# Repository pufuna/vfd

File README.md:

# PUFVFD — преобразователь частоты 1,5 кВт

Вход: 1 фаза 220 В. Выход: 3 фазы 0…220 В, 0…200 Гц. Скалярное (U/f) и бездатчиковое векторное управление, ПИД-регулятор, ЖКИ 20×4 на русском языке, Modbus RTU, Wi-Fi (веб-интерфейс, Modbus TCP), Bluetooth, корпус для 3D-печати.

> **Статус проекта.** Это комплект конструкторской документации и программного обеспечения. Алгоритмы управления проверены на математической модели двигателя, обе прошивки собираются, печатная плата разведена и проходит проверку правил KiCad без замечаний. **Устройство не собиралось, плата не изготавливалась, на реальном железе ничего не испытывалось.** Плата разведена автоматически и не проходила ревью человеком. Подробности — в `docs/01_description.md` (разделы 3.6 и 4.2).
>
> В устройстве действуют опасные напряжения. Сборка и наладка требуют квалификации для работы с сетевым напряжением.

## Состав

| Путь | Содержимое |
|---|---|
| `pdf/` | все документы в PDF одной папкой: схемы, чертежи слоёв платы, карта сверловки, описание, сборка и наладка, руководство, Modbus, параметры, перечень, даташит модуля (пересборка — `python3 tools/make_pdf.py`) |
| `hardware/out/pch1500_eskd.pdf` | комплект схем по ЕСКД: Э1 (структурная), Э3 (принципиальная, 5 листов), ПЭ3 (перечень элементов), Э4 (соединений) |
| `hardware/out/*.svg` | те же листы по отдельности |
| `hardware/pcb/pch1500_a1.kicad_pcb` | печатная плата (проект KiCad 7) |
| `hardware/pcb/out/` | Gerber и сверловка (`pch1500_a1_gerber.zip`), координаты элементов, чертежи слоёв, отчёт DRC |
| `hardware/out/pch1500.net` | нетлист KiCad |
| `docs/01_description.md` | техническое описание, расчёты, принцип работы |
| `docs/02_assembly.md` | заказ платы, сборка, прошивка, пошаговая наладка |
| `docs/03_user_manual.md` | руководство по эксплуатации: характеристики, подключение, пульт, подробное описание каждого параметра, аварии, Modbus, Wi-Fi/Bluetooth, примеры применения, лист записи настроек (создаётся `python3 tools/make_manual.py` из `tools/manual/` и таблицы параметров прошивки; PDF — `pdf/08_user_manual.pdf`) |
| `docs/04_modbus.md` | карта регистров Modbus, HTTP API |
| `docs/05_printing.md` | печать корпуса на 3D-принтере: какой комплект STL выбрать, материал, настройки, крепёж, сборка |
| `docs/parameters.md` | таблица параметров и кодов аварий (создаётся из прошивки) |
| `docs/bom.md` | перечень элементов с ориентировочными ценами |
| `docs/netlist.md` | таблица цепей платы |
| `firmware/stm32` | прошивка контроллера (STM32F411 Black Pill) |
| `firmware/esp32` | прошивка модуля связи (ESP32) |
| `firmware/bin` | готовые файлы прошивки STM32 и ESP32 и как их записать без PlatformIO |
| `firmware/sim` | модель двигателя и тесты (`make test`) |
| `enclosure/` | корпус 210 × 230 мм: `pch1500_case.scad`; готовые к печати `stl/whole/` (цельный, стол от 235 × 215 мм), `stl/split/` (разрезной, стол 220 × 220 мм), `stl/common/`; `build_stl.sh` — выпуск STL; `check_fit.py` — проверка, что детали платы не задевают корпус, дисплей и кнопки |

## Основные решения

- Силовая часть: мост KBPC3510, шина 3 × 470 мкФ 400 В, интеллектуальный модуль IGBT IKCM30F60GA (600 В, 30 А) с встроенной защитой от КЗ, автономный тормозной ключ.
- Управление: STM32F411 на гальванически развязанной стороне; развязка ШИМ оптронами HCPL-2630, токи — датчиками Холла ACS712, напряжение шины — изолирующим усилителем.
- Связь: ESP32 как необязательный модуль; привод работает и без него.
- Единый источник данных: схема описана в `hardware/netlist.py`; из него получаются чертежи (с автоматической сверкой связности), перечни и плата.
- Ориентировочная стоимость комплектующих — около 14 850 ₽ (см. `docs/bom.md`; цены и наличие по каталогам не сверялись).

## Пересборка

Чертежи и перечни:

```bash
python3 hardware/gen.py
```

```bash
python3 hardware/sch/docs.py
```

Плата (размещение, трассировка, полигоны и DRC, выходные файлы; нужен KiCad 7 с модулем `pcbnew`):

```bash
python3 hardware/pcb/make_pcb.py place
```

```bash
python3 hardware/pcb/make_pcb.py route
```

```bash
python3 hardware/pcb/make_pcb.py finish
```

```bash
hardware/pcb/export.sh
```

Тесты прошивки и таблица параметров:

```bash
make -C firmware/sim test docs
```

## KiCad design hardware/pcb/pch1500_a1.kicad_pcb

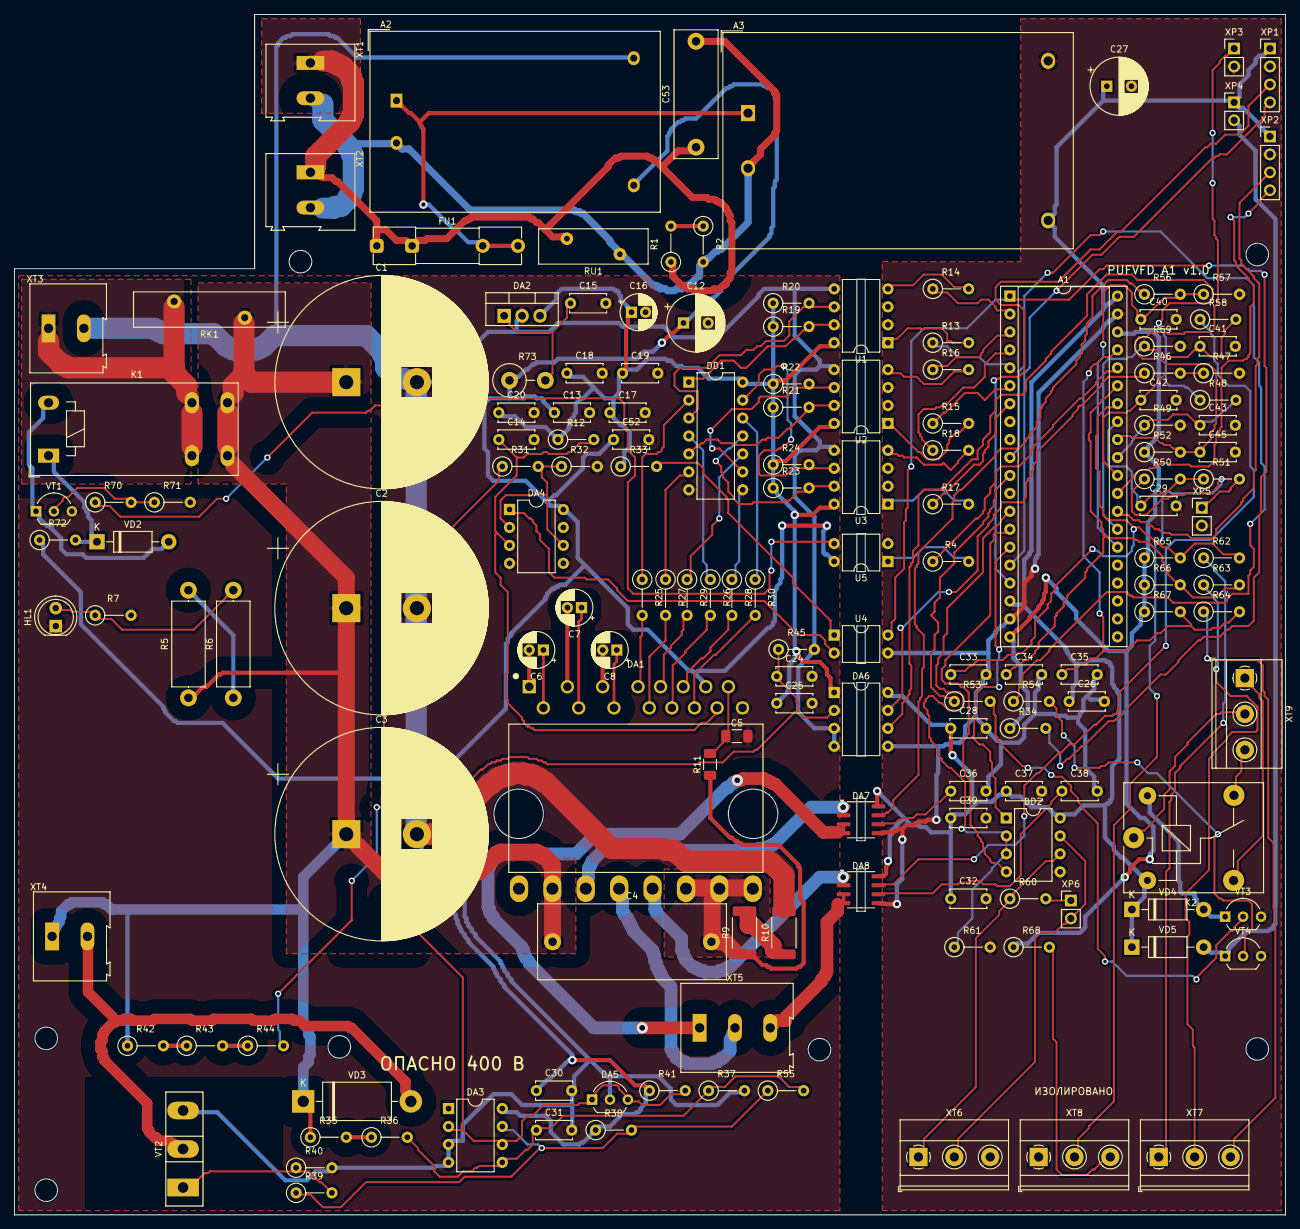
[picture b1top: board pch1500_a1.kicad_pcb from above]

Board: 2 copper layers, 180.0 x 170.0 mm, 164 parts (0 on the bottom side), 119 nets.

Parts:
A1: Black Pill F411; DIP-40_W15.24mm_Socket
A2: HLK-5M15; Converter_ACDC_Hi-Link_HLK-5Mxx
A3: HLK-10M05; Converter_ACDC_Hi-Link_HLK-10Mxx
C1, C2, C3: 470 мкФ 400 В; CP_Radial_D30.0mm_P10.00mm_SnapIn
C4: 0,47 мкФ 630 В; C_Rect_L26.5mm_W10.5mm_P22.50mm_MKS4
C5: 1,5 нФ 1206; C_1206_3216Metric_Pad1.33x1.80mm_HandSolder
C6, C7, C8: 22 мкФ 35 В; CP_Radial_D5.0mm_P2.00mm
C12: 100 мкФ 35 В; CP_Radial_D8.0mm_P3.50mm
C13, C17, C18, C19, C20, C25, C26, C28, C29, C30, C32, C33, C34, C35, C37, C39, C45, C52: 0,1 мкФ; C_Disc_D5.0mm_W2.5mm_P5.00mm
C14, C31, C36, C38, C40, C41, C42, C43: 1 нФ; C_Disc_D5.0mm_W2.5mm_P5.00mm
C15: 0,33 мкФ; C_Disc_D5.0mm_W2.5mm_P5.00mm
C16: 10 мкФ 25 В; CP_Radial_D5.0mm_P2.00mm
C24: 10 нФ; C_Disc_D5.0mm_W2.5mm_P5.00mm
C27: 470 мкФ 10 В; CP_Radial_D8.0mm_P3.50mm
C53: 0,1 мкФ X2; C_Rect_L18.0mm_W6.0mm_P15.00mm_FKS3_FKP3
DA1: IKCM30F60GA; CIPOS_Mini_DIP36x21
DA2: L7805CV; TO-220-3_Vertical
DA3, DA4: LM393; DIP-8_W7.62mm
DA5: TL431; TO-92_Inline_Wide
DA6: HCPL-7840; DIP-8_W7.62mm
DA7, DA8: ACS712ELCTR-30A; SOIC-8_3.9x4.9mm_P1.27mm
DD1: 74HC14; DIP-14_W7.62mm
DD2: MAX485; DIP-8_W7.62mm
FU1: 1 А; Fuseholder_Clip-5x20mm_Littelfuse_111_Inline_P20.00x5.00mm_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
H1, H2, H3, H4, H5, H6, H7: MountingHole_3.2mm_M3
HL1: красный 5 мм; LED_D5.0mm
K1: HF115F-012-1HS3; Relay_SPST_Schrack-RT1-16A-FormA_RM5mm
K2: SRD-05VDC-SL-C; Relay_SPDT_SANYOU_SRD_Series_Form_C
R1, R2: 470 кОм; R_Axial_DIN0207_L6.3mm_D2.5mm_P5.08mm_Vertical
R4: 470 Ом; R_Axial_DIN0207_L6.3mm_D2.5mm_P5.08mm_Vertical
R5, R6: 33 кОм 2 Вт; R_Axial_DIN0414_L11.9mm_D4.5mm_P15.24mm_Horizontal
R7, R19, R20, R21, R22, R23, R24, R53, R54, R62, R63, R64, R70: 1 кОм; R_Axial_DIN0207_L6.3mm_D2.5mm_P5.08mm_Vertical
R9, R10: 0,01 Ом 2512; R_2512_6332Metric_Pad1.40x3.35mm_HandSolder
R11: 1 кОм 1206; R_1206_3216Metric_Pad1.30x1.75mm_HandSolder
R12, R41, R65, R66, R67: 4,7 кОм; R_Axial_DIN0207_L6.3mm_D2.5mm_P5.08mm_Vertical
R13, R14, R15, R16, R17, R18: 150 Ом; R_Axial_DIN0207_L6.3mm_D2.5mm_P5.08mm_Vertical
R25, R26, R27, R28, R29, R30, R68: 100 Ом; R_Axial_DIN0207_L6.3mm_D2.5mm_P5.08mm_Vertical
R31: 22 кОм; R_Axial_DIN0207_L6.3mm_D2.5mm_P5.08mm_Vertical
R32: 6,8 кОм; R_Axial_DIN0207_L6.3mm_D2.5mm_P5.08mm_Vertical
R33: 680 Ом; R_Axial_DIN0207_L6.3mm_D2.5mm_P5.08mm_Vertical
R34, R40, R61, R71: 10 кОм; R_Axial_DIN0207_L6.3mm_D2.5mm_P5.08mm_Vertical
R35, R36: 470 кОм 1 %; R_Axial_DIN0207_L6.3mm_D2.5mm_P5.08mm_Vertical
R37: 6,2 кОм 1 %; R_Axial_DIN0207_L6.3mm_D2.5mm_P5.08mm_Vertical
R38: 2,2 кОм; R_Axial_DIN0207_L6.3mm_D2.5mm_P5.08mm_Vertical
R39: 22 Ом; R_Axial_DIN0207_L6.3mm_D2.5mm_P5.08mm_Vertical
R42, R43, R44: 330 кОм 1 %; R_Axial_DIN0207_L6.3mm_D2.5mm_P5.08mm_Vertical
R45: 390 Ом 1 %; R_Axial_DIN0207_L6.3mm_D2.5mm_P5.08mm_Vertical
R46, R47, R48, R49, R51, R52, R56, R58: 10 кОм 1 %; R_Axial_DIN0207_L6.3mm_D2.5mm_P5.08mm_Vertical
R50, R57, R59: 20 кОм 1 %; R_Axial_DIN0207_L6.3mm_D2.5mm_P5.08mm_Vertical
R55: 1 МОм; R_Axial_DIN0207_L6.3mm_D2.5mm_P5.08mm_Vertical
R60: 120 Ом; R_Axial_DIN0207_L6.3mm_D2.5mm_P5.08mm_Vertical
R72: 82 Ом 0,5 Вт; R_Axial_DIN0207_L6.3mm_D2.5mm_P5.08mm_Vertical
R73: 47 Ом 2 Вт; R_Axial_DIN0414_L11.9mm_D4.5mm_P5.08mm_Vertical
RK1: NTC 10D-20; RV_Disc_D21.5mm_W5mm_P10mm
RU1: 14D471K; RV_Disc_D15.5mm_W5mm_P7.5mm
U1, U2, U3: HCPL-2630; DIP-8_W7.62mm
U4, U5: PC817; DIP-4_W7.62mm
VD2, VD4, VD5: 1N4007; D_DO-41_SOD81_P10.16mm_Horizontal
VD3: UF5408; D_DO-201AD_P15.24mm_Horizontal
VT1, VT3, VT4: BC337-40; TO-92_Inline_Wide
VT2: FGH40N60SMD; TO-247-3_Vertical
XP1: ПУЛЬТ; PinHeader_1x04_P2.54mm_Vertical
XP2: ESP32; PinHeader_1x04_P2.54mm_Vertical
XP3: NTC; PinHeader_1x02_P2.54mm_Vertical
XP4: FAN; PinHeader_1x02_P2.54mm_Vertical
XP5: 0-10V; PinHeader_1x02_P2.54mm_Vertical
XP6: TERM; PinHeader_1x02_P2.54mm_Vertical
XT1: L N; TerminalBlock_Altech_AK300-2_P5.00mm
XT2: ~ ~; TerminalBlock_Altech_AK300-2_P5.00mm
XT3: + -; TerminalBlock_Altech_AK300-2_P5.00mm
XT4: R торм.; TerminalBlock_Altech_AK300-2_P5.00mm
XT5: U V W; TerminalBlock_Altech_AK300-3_P5.00mm
XT6: A B GND; TerminalBlock_Phoenix_MKDS-1,5-3-5.08_1x03_P5.08mm_Horizont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
XT7: DI1 DI2 DI3; TerminalBlock_Phoenix_MKDS-1,5-3-5.08_1x03_P5.08mm_Horizont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
XT8: GND AI 3V3; TerminalBlock_Phoenix_MKDS-1,5-3-5.08_1x03_P5.08mm_Horizont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
XT9: РЕЛЕ; TerminalBlock_Phoenix_MKDS-1,5-3-5.08_1x03_P5.08mm_Horizont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

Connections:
+3V3: A1.20, A1.38, R34.1, R52.1, R65.1, R66.1, R67.1, R68.1
+5V: A1.18, A1.40, A3.4, C26.1, C27.1, C28.1, C32.1, C37.1, C39.1, DA6.8, DA7.8, DA8.8, DD2.8, K2.2, VD4.1, VD5.1, XP1.1, XP2.1, XP4.1
+5VH: C16.1, C17.1, C18.1, C19.1, C20.1, C25.1, DA2.3, DA6.1, DD1.14, R12.1, R19.1, R20.1, R21.1, R22.1, R23.1, R24.1, R33.1, U1.8, U2.8, U3.8
+15VH: A2.4, C12.1, C13.1, C30.1, C52.1, DA1.13, DA3.8, DA4.8, R38.1, R41.1, R72.1, R73.1, U5.4
AI: A1.33, C29.1, R50.2, R51.1
AI_D: R51.2, XP5.1
AI_X: R50.1, XT8.2
BLD: R5.2, R6.1
BR+: K1.11, RK1.1, XT3.1
BRK_C: VD3.2, VT2.2, XT4.2
BRK_D: R35.2, R36.1
BRK_G: DA3.7, R38.2, R39.1, R55.1
BRK_GQ: R39.2, R40.1, VT2.1
BRK_S: C31.1, DA3.5, R36.2, R37.1, R55.2
DCP: C1.1, C2.1, C3.1, C4.1, DA1.23, K1.14, R5.1, R35.1, R42.1, RK1.2, VD3.1, XT4.1
DE: A1.13, DD2.2, DD2.3, R61.1
DI1: A1.34, C33.1, R62.2, R65.2
DI1_X: R62.1, XT7.1
DI2: A1.35, C34.1, R63.2, R66.2
DI2_X: R63.1, XT7.2
DI3: A1.37, C35.1, R64.2, R67.2
DI3_X: R64.1, XT7.3
FAN: A1.10, R54.1
FANB: R54.2, VT4.2
FAN_N: VD5.2, VT4.1, XP4.2
FAULT_N: A1.1, R34.2, U4.4
FLT_A: R33.2, U4.1
FLT_K: DA4.1, U4.2
FLT_U: C36.1, DA7.6
FLT_W: C38.1, DA8.6
GND: A1.19, A1.39, A3.3, C26.2, C27.2, C28.2, C29.2, C32.2, C33.2, C34.2, C35.2, C36.2, C37.2, C38.2, C39.2, C40.2, C41.2, C42.2, C43.2, C45.2, DA6.5, DA7.5, DA8.5, DD2.5, R47.2, R49.2, R57.2, R59.2, R61.2, U1.2, U1.3, U2.2, U2.3, U3.2, U3.3, U4.3, U5.2, VT3.3, VT4.3, XP1.2, XP2.2, XP3.2, XP5.2, XT6.3, XT8.1
GNDH: A2.3, C1.2, C2.2, C3.2, C5.2, C12.2, C13.2, C14.2, C15.2, C16.2, C17.2, C18.2, C19.2, C20.2, C24.2, C25.2, C30.2, C31.2, C52.2, DA1.16, DA2.2, DA3.3, DA3.4, DA4.4, DA4.5, DA5.2, DA6.3, DA6.4, DD1.7, HL1.1, R7.2, R10.2, R32.2, R37.2, R40.2, R45.2, R71.2, U1.5, U2.5, U3.5, VT1.3, VT2.3, XT3.2
HU: DA1.7, R25.2
HV: DA1.8, R27.2
HW: DA1.9, R29.2
IN0: DD1.2, R25.1
IN1: DD1.4, R26.1
IN2: DD1.6, R27.1
IN3: DD1.8, R28.1
IN4: DD1.10, R29.1
IN5: DD1.12, R30.1
ITRIP: C5.1, DA1.15, R11.2
IU: A1.26, C40.1, R56.2, R57.1
IU_5: DA7.7, R56.1
IW: A1.27, C41.1, R58.2, R59.1
IW_5: DA8.7, R58.1
K1A: R4.2, U5.1
K1B: R70.2, R71.1, VT1.2
K1C: K1.A2, VD2.2, VT1.1
K1E: R70.1, U5.3
K1P: K1.A1, R72.2, VD2.1
K2B: R53.2, VT3.2
K2C: K2.5, VD4.2, VT3.1
LA0: R13.2, U1.1
LA1: R14.2, U1.4
LA2: R15.2, U2.1
LA3: R16.2, U2.4
LA4: R17.2, U3.1
LA5: R18.2, U3.4
LEDA: HL1.2, R6.2, R7.1
LU: DA1.10, R26.2
LV: DA1.11, R28.2
LW: DA1.12, R30.2
L_AUX: A2.1, A3.1, FU1.2
L_IN: C53.1, FU1.1, R1.1, RU1.1, XT1.1, XT2.1
NSH: C4.2, DA1.17, DA1.18, DA1.19, R9.1, R11.1
NTC: A1.32, C45.1, R52.2, XP3.1
N_IN: A2.2, A3.2, C53.2, R2.2, RU1.2, XT1.2, XT2.2
OC0: DD1.1, R19.2, U1.7
OC1: DD1.3, R20.2, U1.6
OC2: DD1.5, R21.2, U2.7
OC3: DD1.9, R22.2, U2.6
OC4: DD1.11, R23.2, U3.7
OC5: DD1.13, R24.2, U3.6
P15D: C15.1, DA2.1, R73.2
PRECH: A1.36, R4.1
PWM_UH: A1.5, R13.1
PWM_UL: A1.2, R14.1
PWM_VH: A1.6, R15.1
PWM_VL: A1.3, R16.1
PWM_WH: A1.7, R17.1
PWM_WL: A1.4, R18.1
REF06: DA4.2, DA4.6, R31.2, R32.1
REF25: DA3.2, DA3.6, DA5.1, DA5.3, R31.1, R41.2
REF_X: R68.2, XT8.3
RLY: A1.11, R53.1
RL_COM: K2.1, XT9.2
RL_NC: K2.4, XT9.3
RL_NO: K2.3, XT9.1
RS_A: DD2.6, R60.1, XT6.1
RS_B: DD2.7, XP6.2, XT6.2
RS_T: R60.2, XP6.1
RX485: A1.15, DD2.1
RX_ESP: A1.29, XP2.4
SCL: A1.16, XP1.4
SDA: A1.17, XP1.3
SHM: R9.2, R10.1
TX485: A1.14, DD2.4
TX_ESP: A1.28, XP2.3
U_IPM: DA1.22, DA7.1, DA7.2
U_OUT: DA7.3, DA7.4, XT5.1
VBN: A1.31, C43.1, R48.2, R49.1
VBP: A1.30, C42.1, R46.2, R47.1
VBU: C6.1, DA1.2
VBV: C7.1, DA1.4
VBW: C8.1, DA1.6
VD_A: R42.2, R43.1
VD_B: R43.2, R44.1
VFO: C14.1, DA1.14, DA4.3, R12.2
VO_N: DA6.6, R48.1
VO_P: DA6.7, R46.1
VSNS: C24.1, DA6.2, R44.2, R45.1
VSU: C6.2, DA1.1
VSV: C7.2, DA1.3
VSW: C8.2, DA1.5
V_OUT: DA1.21, XT5.2
W_MOT: DA8.3, DA8.4, XT5.3
W_OUT: DA1.20, DA8.1, DA8.2
X2D: R1.2, R2.1

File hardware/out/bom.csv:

Раздел;Поз.;Номинал / тип;Описание;Кол.;Цена, руб;Сумма, руб
Плата;XT1;L N;Клеммник сети 220 В, 2 конт., шаг 5 мм, 24 А;1;90;90
Плата;XT2;~ ~;Клеммник к диодному мосту VD1;1;90;90
Плата;XT3;+ -;Клеммник от диодного моста VD1;1;90;90
Плата;FU1;1 А;Предохранитель 5x20 мм 1 А;1;60;60
Плата;RU1;14D471K;Варистор 300 В~;1;40;40
Плата;C53;0,1 мкФ X2;Конденсатор помехоподавляющий X2 275 В~, шаг выводов 15 мм;1;40;40
Плата;R1, R2;470 кОм;Резистор 0,5 Вт;2;5;10
Плата;RK1;NTC 10D-20;Термистор NTC 10 Ом, диаметр 20 мм;1;60;60
Плата;K1;HF115F-012-1HS3;Реле 16 А, катушка 12 В;1;250;250
Плата;R72;82 Ом 0,5 Вт;Резистор 0,5 Вт;1;5;5
Плата;VT1;BC337-40;Транзистор NPN 45 В 0,8 А;1;10;10
Плата;VD2, VD4, VD5;1N4007;Диод;3;5;15
Плата;U5, U4;PC817;Оптрон транзисторный, DIP-4;2;10;20
Плата;R4;470 Ом;Резистор 0,25 Вт;1;3;3
Плата;R70, R7, R19, R20, R21, R22, R23, R24, R62, R63, R64, R53, R54;1 кОм;Резистор 0,25 Вт;13;3;39
Плата;R71, R34, R40, R61;10 кОм;Резистор 0,25 Вт;4;3;12
Плата;C1, C2, C3;470 мкФ 400 В;Конденсатор электролитический 105 °C, диаметр 30 мм, высота до 50 мм, snap-in, шаг 10 мм;3;380;1140
Плата;R5, R6;33 кОм 2 Вт;Резистор 2 Вт;2;12;24
Плата;HL1;красный 5 мм;Светодиод «ШИНА ПОД НАПРЯЖЕНИЕМ»;1;5;5
Плата;DA1;IKCM30F60GA;Интеллектуальный силовой модуль IGBT 600 В 30 А;1;900;900
Плата;C4;0,47 мкФ 630 В;Конденсатор плёночный полипропиленовый;1;90;90
Плата;R9, R10;0,01 Ом 2512;Резистор-шунт SMD 2512, 2 Вт, 1 %;2;40;80
Плата;R11;1 кОм 1206;Резистор SMD 1206;1;3;3
Плата;C5;1,5 нФ 1206;Конденсатор керамический SMD 1206, 50 В, NP0/X7R;1;4;4
Плата;C6, C7, C8;22 мкФ 35 В;Конденсатор электролитический 105 °C, диаметр 5 мм;3;10;30
Плата;C12;100 мкФ 35 В;Конденсатор электролитический;1;15;15
Плата;C13;0,1 мкФ;Конденсатор керамический 50 В;1;4;4
Плата;R12, R41, R65, R66, R67;4,7 кОм;Резистор 0,25 Вт;5;3;15
Плата;C14;1 нФ;Конденсатор керамический 50 В;1;4;4
Плата;DA7, DA8;ACS712ELCTR-30A;Датчик тока на эффекте Холла ±30 А, SOIC-8;2;250;500
Плата;C36, C38, C31, C40, C41, C42, C43;1 нФ;Конденсатор керамический;7;4;28
Плата;C37, C39, C18, C19, C20, C17, C52, C30, C28, C25, C26, C32, C33, C34, C35, C29, C45;0,1 мкФ;Конденсатор керамический;17;4;68
Плата;XT5;U V W;Клеммник двигателя, 3 конт., шаг 5 мм, 24 А;1;130;130
Плата;U1, U2, U3;HCPL-2630;Оптрон сдвоенный быстродействующий 10 Мбит/с, DIP-8;3;180;540
Плата;R13, R14, R15, R16, R17, R18;270 Ом;Резистор 0,25 Вт;6;3;18
Плата;R25, R26, R27, R28, R29, R30, R68;100 Ом;Резистор 0,25 Вт;7;3;21
Плата;DD1;74HC14;6 инверторов с триггером Шмитта, DIP-14;1;35;35
Плата;DA4, DA3;LM393;Сдвоенный компаратор, DIP-8;2;25;50
Плата;DA5;TL431;Источник опорного напряжения 2,5 В, TO-92;1;12;12
Плата;R31;22 кОм;Резистор 0,25 Вт 1 %;1;3;3
Плата;R32;6,8 кОм;Резистор 0,25 Вт 1 %;1;3;3
Плата;R33;680 Ом;Резистор 0,25 Вт;1;3;3
Плата;A2;HLK-5M15;Модуль питания AC/DC 15 В 5 Вт;1;450;450
Плата;A3;HLK-10M05;Модуль питания AC/DC 5 В 10 Вт;1;600;600
Плата;DA2;78L05;Стабилизатор 5 В 100 мА, TO-92;1;12;12
Плата;C15;0,33 мкФ;Конденсатор керамический;1;4;4
Плата;C16;10 мкФ 25 В;Конденсатор электролитический;1;6;6
Плата;C27;470 мкФ 10 В;Конденсатор электролитический;1;15;15
Плата;DA6;HCPL-7840;Изолирующий усилитель;1;380;380
Плата;R42, R43, R44;330 кОм 1 %;Резистор 0,5 Вт 1 %;3;5;15
Плата;R45;390 Ом 1 %;Резистор 0,25 Вт 1 %;1;3;3
Плата;C24;10 нФ;Конденсатор керамический;1;4;4
Плата;R46, R47, R48, R49, R56, R58, R51, R52;10 кОм 1 %;Резистор 0,25 Вт;8;3;24
Плата;R35, R36;470 кОм 1 %;Резистор 0,5 Вт 1 %;2;5;10
Плата;R37;6,2 кОм 1 %;Резистор 0,25 Вт 1 %;1;3;3
Плата;R55;1 МОм;Резистор 0,25 Вт;1;3;3
Плата;R38;2,2 кОм;Резистор 0,25 Вт;1;3;3
Плата;R39;22 Ом;Резистор 0,25 Вт;1;3;3
Плата;VT2;FGH40N60SMD;IGBT 600 В 40 А, TO-247;1;250;250
Плата;VD3;MUR860;Диод быстрый 600 В 8 А, TO-220-2;1;60;60
Плата;XT4;R торм.;Клеммник тормозного резистора;1;90;90
Плата;A1;Black Pill F411;Плата WeAct Black Pill STM32F411CEU6;1;550;550
Плата;R57, R59, R50;20 кОм 1 %;Резистор 0,25 Вт;3;3;9
Плата;DD2;MAX485;Приёмопередатчик RS-485, DIP-8;1;40;40
Плата;R60;120 Ом;Резистор 0,25 Вт;1;3;3
Плата;XP6;TERM;Перемычка терминатора RS-485;1;5;5
Плата;XT6;A B GND;Клеммник RS-485;1;45;45
Плата;XP1;ПУЛЬТ;Разъём пульта;1;8;8
Плата;XP2;ESP32;Разъём модуля связи ESP32;1;8;8
Плата;XT7;DI1 DI2 DI3;Клеммник дискретных входов;1;45;45
Плата;XT8;GND AI 3V3;Клеммник аналогового входа / потенциометра;1;45;45
Плата;XP5;0-10V;Перемычка: замкнута — вход 0–10 В, разомкнута — потенциометр 0–3,3 В;1;5;5
Плата;XP3;NTC;Разъём термистора радиатора NTC 10 кОм B3950;1;5;5
Плата;K2;SRD-05VDC-SL-C;Реле 10 А, катушка 5 В;1;80;80
Плата;VT3, VT4;BC337-40;Транзистор NPN;2;10;20
Плата;XT9;РЕЛЕ;Клеммник выходного реле;1;45;45
Плата;XP4;FAN;Разъём вентилятора 5 В;1;5;5
Прочее;VD1;KBPC3510;Диодный мост 35 А 1000 В (на радиаторе);1;220;220
Прочее;A4;ESP32 DevKit V1 (ESP32-WROOM-32, 30 или 38 выв.);Модуль связи Wi-Fi/Bluetooth;1;500;500
Прочее;A5;LCD 2004 + I2C-адаптер PCF8574;Жидкокристаллический индикатор 20x4 с подсветкой;1;600;600
Прочее;A6;Модуль PCF8574 (расширитель I2C, адрес 0x20);Опрос кнопок пульта;1;150;150
Прочее;SB1–SB5;Кнопка тактовая 12x12 мм с колпачком;Кнопки пульта: ПУСК, СТОП, ▲, ▼, ВВОД;5;20;100
Прочее;RK2;NTC 10 кОм B3950 с наконечником под винт М3;Датчик температуры радиатора;1;80;80
Прочее;M1;Вентилятор 50x50x10 мм, 5 В;Обдув радиатора;1;250;250
Прочее;—;Радиатор алюминиевый ребристый 125x150 мм, рёбра 20–30 мм (≤1,2 °C/Вт с обдувом);Охлаждение DA1, VD1;1;900;900
Прочее;RB1;Резистор 100 Ом 100–200 Вт в алюминиевом корпусе (RX24 / AH);Тормозной резистор (опция);1;500;500
Прочее;RP1;Потенциометр 10 кОм линейный с ручкой;Задатчик частоты (опция);1;80;80
Прочее;—;Печатная плата PUFVFD.01, двусторонняя 180x135 мм, 1,6 мм, медь 70 мкм (2 oz);Изготовление на заказ;1;2000;2000
Прочее;—;Панельки PBS-20 (2 шт.), DIP-8 (6 шт.), DIP-14, DIP-4 (2 шт.);Установка микросхем и платы A1;1;150;150
Прочее;—;Радиатор для TO-247 П-образный (на VT2);Охлаждение тормозного ключа;1;60;60
Прочее;—;Термопаста КПТ-8;Монтаж на радиатор;1;100;100
Прочее;—;Провод ПуГВ 2,5 мм² (сеть, мост, двигатель, PE), МГТФ/шлейф для пульта, наконечники;Монтаж;1;400;400
Прочее;—;Кабельные вводы PG11 (3 шт.), PG7 (2 шт.), крепёж М3/М4, стойки;Монтаж;1;350;350
Прочее;—;Пластик PETG ≈450 г (корпус);Печать корпуса;1;700;700
Прочее;QF1;Автоматический выключатель 1P C20 (вне корпуса, в щитке);Защита линии питания — обязательна;1;300;300

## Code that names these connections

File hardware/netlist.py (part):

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add("R72", "82 Ом 0,5 Вт", "Резистор 0,5 Вт (катушка 12 В от 15 В)", R_, ["+15VH", "K1P"], 5, S)
add("VT1", "BC337-40", "Транзистор NPN 45 В 0,8 А", "Package_TO_SOT_THT:TO-92_Inline_Wide", {"1:C": "K1C", "2:B": "K1B", "3:E": "GNDH"}, 10, S)
add("VD2", "1N4007", "Диод (гашение ЭДС катушки K1)", "Diode_THT:D_DO-41_SOD81_P10.16mm_Horizontal", {"1:K": "K1P", "2:A": "K1C"}, 5, S)
add("U17", "PC817", "Оптрон транзисторный, DIP-4 (управление реле K1)", "Package_DIP:DIP-4_W7.62mm", {"1:A": "K1A", "2:K": "GND", "3:E": "K1E", "4:C": "+15VH"}, 10, S)
add("R4", "470 Ом", "Резистор 0,25 Вт (светодиод оптрона U17)", R_, ["PRECH", "K1A"], 3, S)
add("R70", "1 кОм", "Резистор 0,25 Вт (база VT1)", R_, ["K1E", "K1B"], 3, S)
add("R71", "10 кОм", "Резистор 0,25 Вт (база VT1 — GNDH)", R_, ["K1B", "GNDH"], 3, S)
for i in (1, 2, 3):
    add(f"C{i}", "470 мкФ 400 В", "Конденсатор электролитический 105 °C, диаметр 30 мм, высота до 50 мм, snap-in, шаг 10 мм, допустимый ток пульсаций не менее 2,5 А (100 Гц)", "Capacitor_THT:CP_Radial_D30.0mm_P10.00mm_SnapIn", {"1:+": "DCP", "2:-": "GNDH"}, 380, S)
add("R5", "33 кОм 2 Вт", "Резистор 2 Вт (разряд шины)", R2W, ["DCP", "BLD"], 12, S)
add("R6", "33 кОм 2 Вт", "Резистор 2 Вт (разряд шины)", R2W, ["BLD", "LEDA"], 12, S)
add("R7", "1 кОм", "Резистор 0,25 Вт (шунтирует светодиод: разряд шины сохраняется при его обрыве)", R_, ["LEDA", "GNDH"], 3, S)
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add("R41", "4,7 кОм", "Резистор 0,25 Вт (ток TL431)", R_, ["+15VH", "REF25"], 3, S)
add("R31", "22 кОм", "Резистор 0,25 Вт 1 %", R_, ["REF25", "REF06"], 3, S)
add("R32", "6,8 кОм", "Резистор 0,25 Вт 1 %", R_, ["REF06", "GNDH"], 3, S)
add("U11", "PC817", "Оптрон транзисторный, DIP-4 (сигнал аварии)", "Package_DIP:DIP-4_W7.62mm", {"1:A": "FLT_A", "2:K": "FLT_K", "3:E": "GND", "4:C": "FAULT_N"}, 10, S)
add("R33", "680 Ом", "Резистор 0,25 Вт", R_, ["+5VH", "FLT_A"], 3, S)
add("R34", "10 кОм", "Резистор 0,25 Вт (подтяжка FAULT)", R_, ["+3V3", "FAULT_N"], 3, S)

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
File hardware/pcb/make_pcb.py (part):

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             '(rule "isolation_barrier" (condition "A.NetClass == \'ISO\' && (B.NetClass == \'HOT\' || B.NetClass == \'HV\' || B.NetClass == \'MAINS\' || B.NetClass == \'LV\' || B.NetClass == \'P5\')") (constraint clearance (min 2.9mm)))']
    for ph in "UVW":
        rules.append(f'(rule "bootstrap_{ph}" (condition "A.NetName == \'VB{ph}\' && B.NetName == \'VS{ph}\'") (constraint clearance (min 0.4mm)))')
    rules.append('(rule "current_sensor_U" (condition "A.NetName == \'U_IPM\' && B.NetName == \'U_OUT\'") (constraint clearance (min 0.3mm)))')
    rules.append('(rule "current_sensor_W" (condition "A.NetName == \'W_OUT\' && B.NetName == \'W_MOT\'") (constraint clearance (min 0.3mm)))')
    open(FINAL.replace(".kicad_pcb", ".kicad_dru"), "w", encoding="utf-8").write("\n".join(rules) + "\n")


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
